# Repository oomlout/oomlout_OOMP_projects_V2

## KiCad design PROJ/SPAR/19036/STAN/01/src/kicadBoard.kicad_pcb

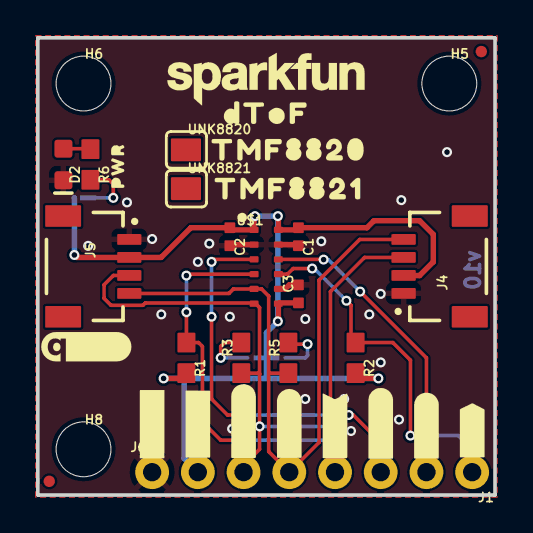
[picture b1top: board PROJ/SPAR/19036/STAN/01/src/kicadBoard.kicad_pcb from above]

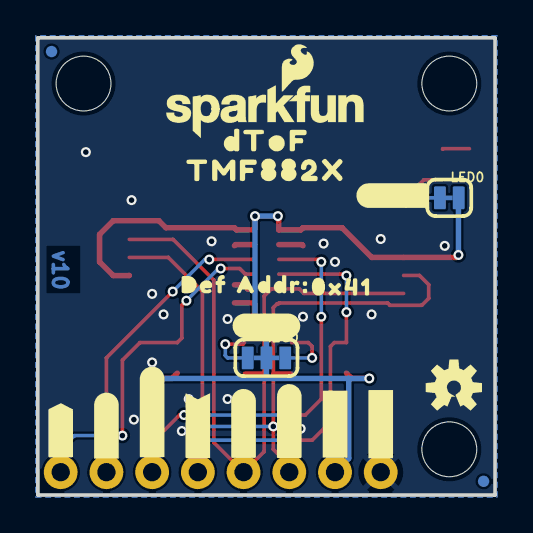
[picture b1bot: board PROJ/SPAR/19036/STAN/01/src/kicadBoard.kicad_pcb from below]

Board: 2 copper layers, 25.4 x 25.4 mm, 57 parts (21 on the bottom side), 12 nets.

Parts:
C1, C2, C3: 0.1uF; 0402-TIGHT
D2: RED; LED-0603
FD5, FD6, FD7, FD8: FIDUCIALUFIDUCIAL; FIDUCIAL-MICRO
FRAME2: FRAME-LETTER; CREATIVE_COMMONS
H5, H6, H8: STAND-OFFTIGHT; STAND-OFF-TIGHT
I2C0: I2C_PU; SMT-JUMPER_3_2-NC_TRACE_SILK
J1, J6: 1X04_NO_SILK
J4, J5: QWIIC_RIGHT_ANGLE; JST04_1MM_RA
LED0: LED; SMT-JUMPER_2_NC_TRACE_SILK
LOGO3: SFE_LOGO_NAME_FLAME.1_INCH; SFE_LOGO_NAME_FLAME_.1
LOGO4: OSHW-LOGOS; OSHW-LOGO-S
R1, R2: 10k; 0603
R3, R5: 2.2k; 0603
R6: 1k; 0603
U$1: TMF882X_TMF8820; TMF882X
U$2, U$16: #3V3#0
U$3, U$18: #GND#4
U$4, U$23: #SDA#6
U$5, U$21: #SCL#5
U$6: QWIIC_LOGO_5MM; QWIIC_5MM
U$7, U$17: #EN#7
U$8: #GP0#19
U$9, U$19: #GP1#8
U$10: ##INT##9
U$11, U$26: DTOF882188211
U$12: TMF88209
U$13: SFE_LOGO_NAME_.1
U$14: PWR882188212
U$15: #SYNC#8
U$20: #I2C#11
U$22: #LED#10
U$24: ##INT##8
U$25: TMF882188210
U$27: TMF882X882188211
U$28: DEF11
U$29: ADDR#12
U$30: 0X4113
UNK8820: PROD_ID_PASTE_SILK; PRODUCT_IDENT_PASTE_SILK
UNK8821: PROD_ID_NO-PASTE_SILK; PRODUCT_IDENT_NO_SILK

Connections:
3.3V: C1.1, C2.1, C3.1, I2C0.2, J4.2, J5.2, J6.2, LED0.2, R1.2, R2.2, U$1.P1, U$1.P7, U$1.P12
EN: J1.1, R2.1, U$1.P9
GND: C1.2, C2.2, C3.2, D2.C, J4.1, J5.1, J6.1, U$1.P2, U$1.P8, U$1.P11
GPIO0/SYNC: J1.3, U$1.P3
GPIO1: J1.2, U$1.P10
unnamed: D2.A, R6.1
unnamed: LED0.1, R6.2
unnamed: I2C0.3, R3.2
unnamed: I2C0.1, R5.2
SCL: J4.4, J5.4, J6.4, R5.1, U$1.P5
SDA: J4.3, J5.3, J6.3, R3.1, U$1.P6
~INT: J1.4, R1.1, U$1.P4

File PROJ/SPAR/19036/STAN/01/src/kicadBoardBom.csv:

"Id";"Designator";"Package";"Quantity";"Designation";"Supplier and ref";
1;"R6";"0603";1;"1k";;;
2;"U$10";"##INT##9";1;"";;;
3;"U$8";"#GP0#19";1;"";;;
4;"J5,J4";"JST04_1MM_RA";2;"QWIIC_RIGHT_ANGLE";;;
5;"FD8,FD7,FD5,FD6";"FIDUCIAL-MICRO";4;"FIDUCIALUFIDUCIAL";;;
6;"U$12";"TMF88209";1;"";;;
7;"J1,J6";"1X04_NO_SILK";2;"";;;
8;"H8,H6,H5";"STAND-OFF-TIGHT";3;"STAND-OFFTIGHT";;;
9;"U$9,U$19";"#GP1#8";2;"";;;
10;"R3,R5";"0603";2;"2.2k";;;
11;"UNK8820";"PRODUCT_IDENT_PASTE_SILK";1;"PROD_ID_PASTE_SILK";;;
12;"U$13";"SFE_LOGO_NAME_.1";1;"";;;
13;"R1,R2";"0603";2;"10k";;;
14;"C1,C2,C3";"0402-TIGHT";3;"0.1uF";;;
15;"U$11,U$26";"DTOF882188211";2;"";;;
16;"D2";"LED-0603";1;"RED";;;
17;"U$4,U$23";"#SDA#6";2;"";;;
18;"UNK8821";"PRODUCT_IDENT_NO_SILK";1;"PROD_ID_NO-PASTE_SILK";;;
19;"U$17,U$7";"#EN#7";2;"";;;
20;"U$25";"TMF882188210";1;"";;;
21;"FRAME2";"CREATIVE_COMMONS";1;"FRAME-LETTER";;;
22;"U$5,U$21";"#SCL#5";2;"";;;
23;"U$1";"TMF882X";1;"TMF882X_TMF8820";;;
24;"U$14";"PWR882188212";1;"";;;
25;"U$6";"QWIIC_5MM";1;"QWIIC_LOGO_5MM";;;
26;"U$3,U$18";"#GND#4";2;"";;;
27;"U$2,U$16";"#3V3#0";2;"";;;
28;"U$22";"#LED#10";1;"";;;
29;"LED0";"SMT-JUMPER_2_NC_TRACE_SILK";1;"LED";;;
30;"U$29";"ADDR#12";1;"";;;
31;"U$28";"DEF11";1;"";;;
32;"U$24";"##INT##8";1;"";;;
33;"U$27";"TMF882X882188211";1;"";;;
34;"U$30";"0X4113";1;"";;;
35;"LOGO4";"OSHW-LOGO-S";1;"OSHW-LOGOS";;;
36;"U$20";"#I2C#11";1;"";;;
37;"U$15";"#SYNC#8";1;"";;;
38;"I2C0";"SMT-JUMPER_3_2-NC_TRACE_SILK";1;"I2C_PU";;;
39;"LOGO3";"SFE_LOGO_NAME_FLAME_.1";1;"SFE_LOGO_NAME_FLAME.1_INCH";;;

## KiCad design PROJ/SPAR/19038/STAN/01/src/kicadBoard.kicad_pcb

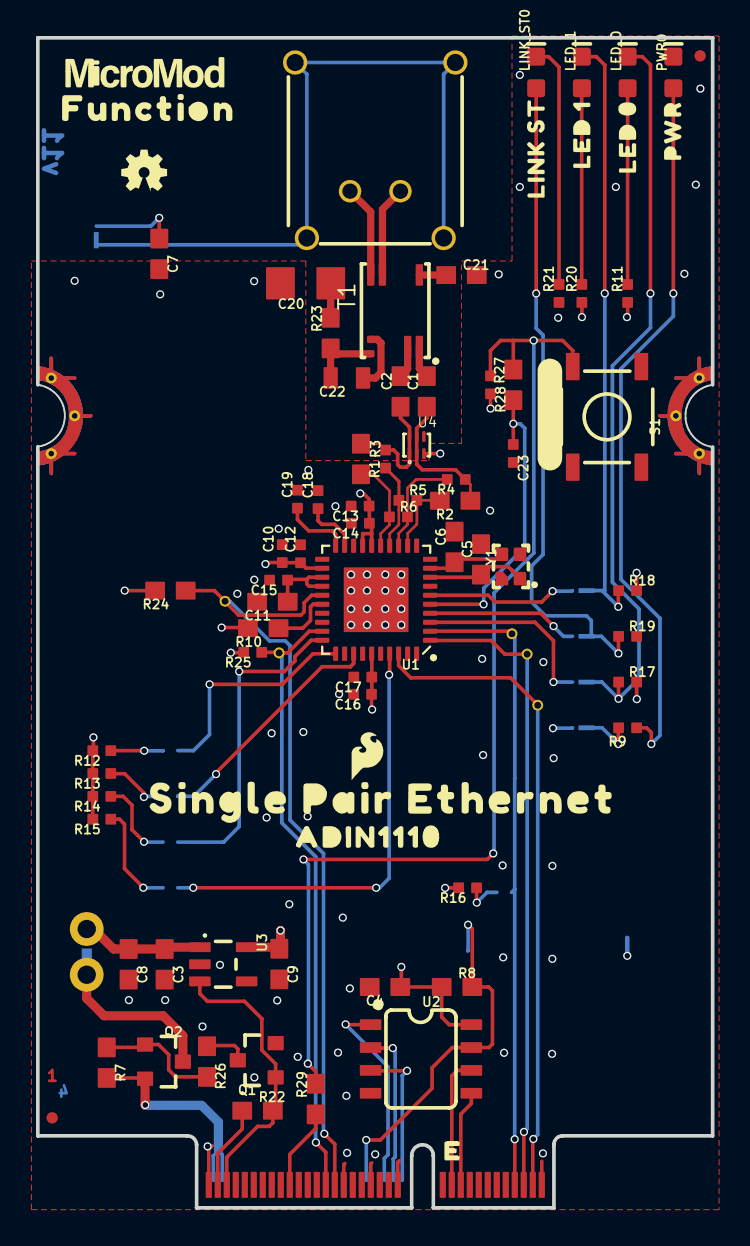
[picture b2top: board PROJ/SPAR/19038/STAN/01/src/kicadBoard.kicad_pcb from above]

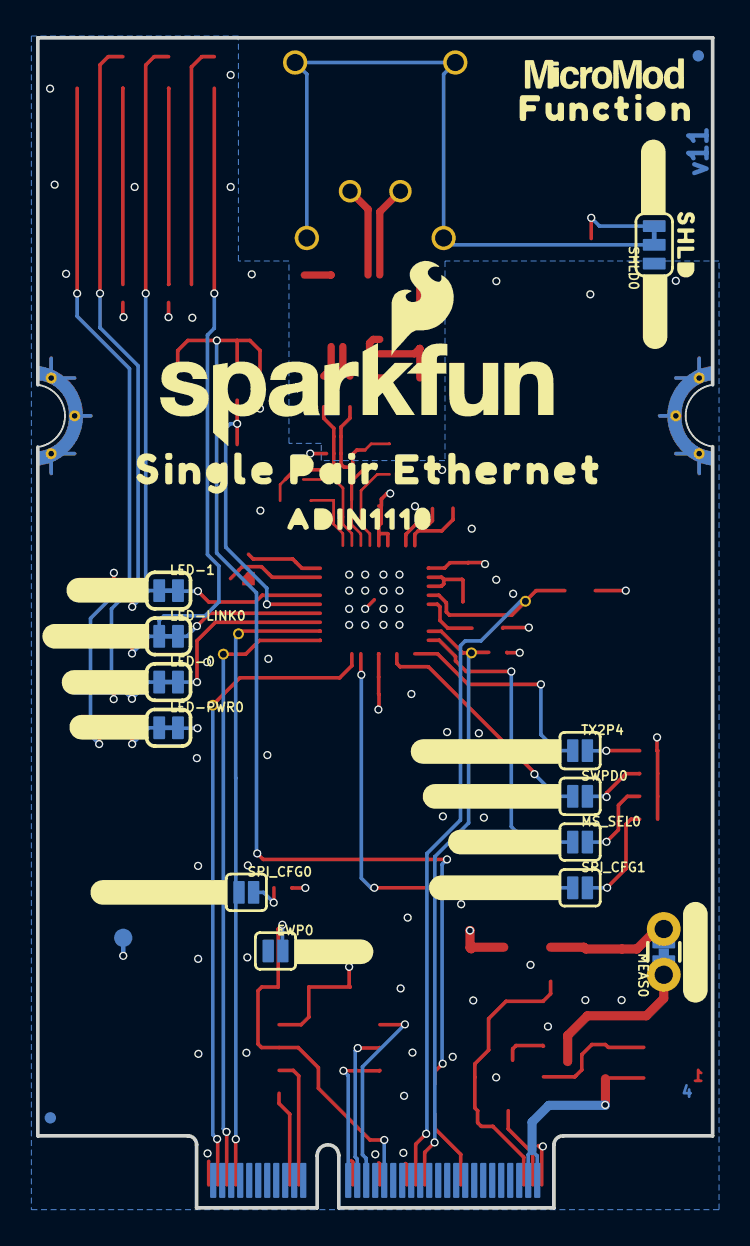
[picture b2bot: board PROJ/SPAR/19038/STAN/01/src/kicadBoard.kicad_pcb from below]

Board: 4 copper layers, 37.5 x 65.0 mm, 121 parts (34 on the bottom side), 65 nets.

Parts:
C1, C2: 0.22uF; 0603
C3, C4: 0.1uF; 0603
C5, C6: 10pF; 0603
C7: 3.3nF; 0603
C8, C9: 1.0uF; 0603
C10, C13, C15, C16, C18, C23: 0.1uF; 0402-TIGHT
C11: 0.68uF; 0603
C12, C14, C17: 10nF; 0402-TIGHT
C19: 1.0uF; 0402-TIGHT
C20: 1.0nF/2kV; 1206
C21: 0.1uF/50V; 0603
C22: 470nF/100V; 0805
CIPO0: TP_15TH
COPI0: TP_15TH
CS0: TP_15TH
EWP0: JUMPER-SMT_2_NO_SILK; SMT-JUMPER_2_NO_SILK
FD1, FD2, FD3, FD4: FIDUCIALUFIDUCIAL; FIDUCIAL-MICRO
FRAME1: FRAME-LEDGER; CREATIVE_COMMONS
INT0: TP_15TH
J1: IP20(RJ50); T1_INDUSTRIAL_JACK_AH_IP20
J2: MICROMOD_FUNCTION_STANDARD; M.2-CARD-E-22_FUNCTION_STANDARD
LED-0, LED-1: JUMPER-SMT_2_NC_TRACE_SILK; SMT-JUMPER_2_NC_TRACE_SILK
LED-LINK0: JUMPER-SMT_2_NC_TRACE_SILK; SMT-JUMPER_2_NC_TRACE_SILK
LED-PWR0: JUMPER-SMT_2_NC_TRACE_SILK; SMT-JUMPER_2_NC_TRACE_SILK
LED_0: Green; LED-0603
LED_1: Yellow; LED-0603
LINK_ST0: Blue; LED-0603
LOGO1: SFE_LOGO_NAME_FLAME.2_INCH; SFE_LOGO_NAME_FLAME_.2
LOGO2: SPECIAL_INSTRUCTIONS-ORDERING; ORDERING_INSTRUCTIONS
LOGO3: OSHW-LOGOMINI; OSHW-LOGO-MINI
MEAS0: JUMPER-COMBO_2_NC_TRACE; COMBO-JUMPER_2_NC_TRACE
MS_SEL0: SMT-JUMPER_2_NO_SILK
PWR0: Red; LED-0603
Q1: 220mA/50V/3.5Ω; SOT23-3
Q2: 20V/4.2A/52mΩ/1.4W; SOT23-3
R1, R2: 49.9; 0603
R3, R4: 5.1k; 0402-TIGHT
R5, R6: 10.2k; 0402-TIGHT
R7, R8, R22: 10k; 0603
R9, R11, R20, R21: 1k; 0402-TIGHT
R10, R24: 1.5k; 0603
R12, R13, R14, R15, R16, R17, R18, R19, R25: 4.7k; 0402-TIGHT
R23, R29: 100Ω; 0603
R26: 100; 0603
R27: 4.7k; 0603
R28: 100k; 0402-TIGHT
S1: RESET; TACTILE_SWITCH_SMD_5.2MM
SHLD0: SMT-JUMPER_3_1-NC_TRACE_SILK
SPI0: TP_15TH
SPI_CFG0, SPI_CFG1: SMT-JUMPER_2_NO_SILK
SWPD0: SMT-JUMPER_2_NO_SILK
T1: WE-STST; WE_STST_TRANSFORMER_1_1_SMD_3.2X4.7MM_74930030
TP1: TEST-POINT3X4; PAD.03X.04
TX2P4: SMT-JUMPER_2_NO_SILK
U1: ADIN1110; LFCSP-40
U2: EEPROM; SO08
U3: 3.3V; SOT23-5
U4: WE-TVS; WE_TVS_1.0X1.2MM
U$1: #RESET#0
U$4, U$21: ADIN11100
U$5: SFE_LOGO_FLAME_.1
U$6: #PWR#19
U$7: PWR0
U$8: SHLD11
U$9: #EWP#18
U$10: #LED0#20
U$11: #GND#16
U$12: #CAP#17
U$13: ##TX2P4_EN##4
U$14: #SPI_CFG1#0
U$15: #MS_SEL#2
U$16: #SPI_CFG0#0
U$17, U$18: SINGLE_PAIR_ETHERNET0
U$22: ##SWPD_EN##4
U$23: LED_03
U$24, U$26: FUNCTION0
U$25: LED_14
U$27: LINK_ST15
U$28: #MEAS#3
U$29: #LED1#21
U$31: #LINKST#2
U$37, U$63: MICROMOD_LOGO_.35
Y1: 25MHz; CRYSTAL-SMD-2.0X1.6MM-WE

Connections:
1.1V: C11.1, C15.1, U1.23, U1.24
3.3V: C4.1, C9.1, C10.1, C12.1, C13.1, C14.1, C16.1, C17.1, LED-PWR0.2, R8.1, R10.2, R11.1, R12.2, R13.2, R14.2, R15.2, R16.2, R17.2, R18.2, R20.1, R24.2, R25.2, R28.2, TP1.1, U1.16, U1.17, U1.22, U1.35, U2.8, U3.5
3.3V_IN: J2.73, R22.1
A0: J2.36, U2.1
A1: J2.34, U2.2
A2: J2.32, U2.3
DA+: J1.1, T1.7
DA-: J1.2, T1.6
EWP: EWP0.2, J2.40, R8.2, U2.7
GND: C3.2, C4.2, C5.2, C6.2, C7.2, C8.2, C9.2, C10.2, C11.2, C12.2, C13.2, C14.2, C15.2, C16.2, C17.2, C18.2, C19.2, C20.2, C21.2, C23.2, EWP0.1, J2.1, J2.33, J2.39, J2.45, J2.75, J2.GND1, J2.GND2, J2.GND3, J2.GND4, J2.GND5, J2.GND6, PWR0.C, Q1.2, R19.2, R21.1, S1.1, SHLD0.1, U1.EP, U2.4, U3.2, U4.3, Y1.2, Y1.4
I2C_SCL: J2.21, U2.6
I2C_SDA: J2.19, U2.5
LED_0: LED-0.2, U1.3
LED_1: LED-1.2, U1.6
LINK_ST: LED-LINK0.2, U1.4
MS_SEL: MS_SEL0.1, U1.30
unnamed: MEAS0.1, MEAS0.3, Q2.3
unnamed: C3.1, C8.1, MEAS0.2, MEAS0.4, U3.1
unnamed: C21.1, T1.5
unnamed: C22.1, T1.4
unnamed: LED-LINK0.1, LINK_ST0.A, R19.1
unnamed: LED-1.1, LED_1.C, R18.1
unnamed: C22.2, R23.1, T1.3
unnamed: C20.1, R23.2
unnamed: LED-0.1, LED_0.C, R17.1
unnamed: Q1.3, R26.1
unnamed: Q2.1, R7.1, R26.2
unnamed: C5.1, U1.8, Y1.1
unnamed: C23.1, R27.1, U1.5
unnamed: C6.1, U1.9, Y1.3
unnamed: R27.2, R28.1, R29.2, S1.3
unnamed: R10.1, U1.26
unnamed: LED-PWR0.1, R9.2
unnamed: PWR0.A, R9.1
unnamed: C18.1, U1.19
unnamed: C19.1, U1.20
unnamed: LED_0.A, R11.2
unnamed: C1.1, R2.1, R4.1, U4.2, U4.5
unnamed: MS_SEL0.2, R14.1
unnamed: R13.1, SWPD0.2
unnamed: R12.1, TX2P4.2
unnamed: R16.1, SPI_CFG0.2
unnamed: R15.1, SPI_CFG1.2
unnamed: LED_1.A, R20.2
unnamed: C2.1, R1.1, R3.2, U4.1, U4.6
unnamed: C1.2, T1.1
unnamed: LINK_ST0.C, R21.2
unnamed: C2.2, T1.2
unnamed: R4.2, R6.2, U1.13
unnamed: R3.1, R5.1, U1.14
unnamed: R1.2, R6.1, U1.15
unnamed: R2.2, R5.2, U1.12
unnamed: C7.1, SHLD0.3
unnamed: J1.S1, J1.S2, J1.S3, J1.S4, SHLD0.2
PWR_EN: J2.71, Q1.1, R22.2, U3.3
SPI_CFG1: SPI_CFG1.1, U1.37
SPI_PICO: COPI0.1, J2.5, U1.1
SPI_POCI/SPI_CFG0: CIPO0.1, J2.7, SPI_CFG0.1, U1.2
SPI_SCK: J2.3, SPI0.1, U1.38
VCC_IN: J2.72, J2.74, Q2.2, R7.2
~CS: CS0.1, J2.49, R25.1, U1.29
~INT: INT0.1, J2.47, R24.1, U1.25
~RESET: J2.57, R29.1
~SWPD_EN: SWPD0.1, U1.33
~TX2P4_EN: TX2P4.1, U1.31

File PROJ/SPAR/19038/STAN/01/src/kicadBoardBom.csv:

"Id";"Designator";"Package";"Quantity";"Designation";"Supplier and ref";
1;"U$27";"LINK_ST15";1;"";;;
2;"R18,R25,R12,R17,R19,R16,R13,R14,R15";"0402-TIGHT";9;"4.7k";;;
3;"FRAME1";"CREATIVE_COMMONS";1;"FRAME-LEDGER";;;
4;"U$7";"PWR0";1;"";;;
5;"C2,C1";"0603";2;"0.22uF";;;
6;"Q2";"SOT23-3";1;"20V/4.2A/52mΩ/1.4W";;;
7;"C8,C9";"0603";2;"1.0uF";;;
8;"U1";"LFCSP-40";1;"ADIN1110";;;
9;"C10,C13,C16,C23,C15,C18";"0402-TIGHT";6;"0.1uF";;;
10;"R20,R11,R9,R21";"0402-TIGHT";4;"1k";;;
11;"R23,R29";"0603";2;"100Ω";;;
12;"CIPO0,INT0,SPI0,COPI0,CS0";"TP_15TH";5;"";;;
13;"R26";"0603";1;"100";;;
14;"S1";"TACTILE_SWITCH_SMD_5.2MM";1;"RESET";;;
15;"R5,R6";"0402-TIGHT";2;"10.2k";;;
16;"U3";"SOT23-5";1;"3.3V";;;
17;"C17,C12,C14";"0402-TIGHT";3;"10nF";;;
18;"LOGO3";"OSHW-LOGO-MINI";1;"OSHW-LOGOMINI";;;
19;"R1,R2";"0603";2;"49.9";;;
20;"LED_1";"LED-0603";1;"Yellow";;;
21;"U$25";"LED_14";1;"";;;
22;"C19";"0402-TIGHT";1;"1.0uF";;;
23;"LED_0";"LED-0603";1;"Green";;;
24;"R7,R22,R8";"0603";3;"10k";;;
25;"U$17,U$18";"SINGLE_PAIR_ETHERNET0";2;"";;;
26;"C5,C6";"0603";2;"10pF";;;
27;"PWR0";"LED-0603";1;"Red";;;
28;"R24,R10";"0603";2;"1.5k";;;
29;"U$5";"SFE_LOGO_FLAME_.1";1;"";;;
30;"FD2,FD1,FD4,FD3";"FIDUCIAL-MICRO";4;"FIDUCIALUFIDUCIAL";;;
31;"T1";"WE_STST_TRANSFORMER_1_1_SMD_3.2X4.7MM_74930030";1;"WE-STST";;;
32;"LOGO2";"ORDERING_INSTRUCTIONS";1;"SPECIAL_INSTRUCTIONS-ORDERING";;;
33;"U$63,U$37";"MICROMOD_LOGO_.35";2;"";;;
34;"U$26,U$24";"FUNCTION0";2;"";;;
35;"R3,R4";"0402-TIGHT";2;"5.1k";;;
36;"U4";"WE_TVS_1.0X1.2MM";1;"WE-TVS";;;
37;"C11";"0603";1;"0.68uF";;;
38;"R27";"0603";1;"4.7k";;;
39;"U$23";"LED_03";1;"";;;
40;"U$1";"#RESET#0";1;"";;;
41;"C3,C4";"0603";2;"0.1uF";;;
42;"Q1";"SOT23-3";1;"220mA/50V/3.5Ω";;;
43;"C20";"1206";1;"1.0nF/2kV";;;
44;"R28";"0402-TIGHT";1;"100k";;;
45;"C7";"0603";1;"3.3nF";;;
46;"U2";"SO08";1;"EEPROM";;;
47;"C22";"0805";1;"470nF/100V";;;
48;"C21";"0603";1;"0.1uF/50V";;;
49;"LINK_ST0";"LED-0603";1;"Blue";;;
50;"Y1";"CRYSTAL-SMD-2.0X1.6MM-WE";1;"25MHz";;;
51;"U$4,U$21";"ADIN11100";2;"";;;
52;"J2";"M.2-CARD-E-22_FUNCTION_STANDARD";1;"MICROMOD_FUNCTION_STANDARD";;;
53;"J1";"T1_INDUSTRIAL_JACK_AH_IP20";1;"IP20(RJ50)";;;
54;"LOGO1";"SFE_LOGO_NAME_FLAME_.2";1;"SFE_LOGO_NAME_FLAME.2_INCH";;;
55;"LED-1,LED-0,LED-LINK0,LED-PWR0";"SMT-JUMPER_2_NC_TRACE_SILK";4;"JUMPER-SMT_2_NC_TRACE_SILK";;;
56;"SPI_CFG0,SPI_CFG1,TX2P4,SWPD0,MS_SEL0";"SMT-JUMPER_2_NO_SILK";5;"";;;
57;"U$8";"SHLD11";1;"";;;
58;"U$15";"#MS_SEL#2";1;"";;;
59;"U$9";"#EWP#18";1;"";;;
60;"U$12";"#CAP#17";1;"";;;
61;"MEAS0";"COMBO-JUMPER_2_NC_TRACE";1;"JUMPER-COMBO_2_NC_TRACE";;;
62;"U$6";"#PWR#19";1;"";;;
63;"TP1";"PAD.03X.04";1;"TEST-POINT3X4";;;
64;"U$29";"#LED1#21";1;"";;;
65;"U$10";"#LED0#20";1;"";;;
66;"U$14";"#SPI_CFG1#0";1;"";;;
67;"U$22";"##SWPD_EN##4";1;"";;;
68;"EWP0";"SMT-JUMPER_2_NO_SILK";1;"JUMPER-SMT_2_NO_SILK";;;
69;"U$13";"##TX2P4_EN##4";1;"";;;
70;"U$28";"#MEAS#3";1;"";;;
71;"SHLD0";"SMT-JUMPER_3_1-NC_TRACE_SILK";1;"";;;
72;"U$11";"#GND#16";1;"";;;
73;"U$31";"#LINKST#2";1;"";;;
74;"U$16";"#SPI_CFG0#0";1;"";;;

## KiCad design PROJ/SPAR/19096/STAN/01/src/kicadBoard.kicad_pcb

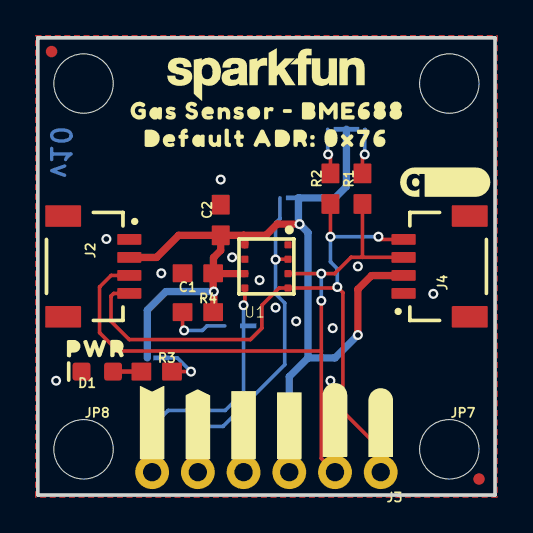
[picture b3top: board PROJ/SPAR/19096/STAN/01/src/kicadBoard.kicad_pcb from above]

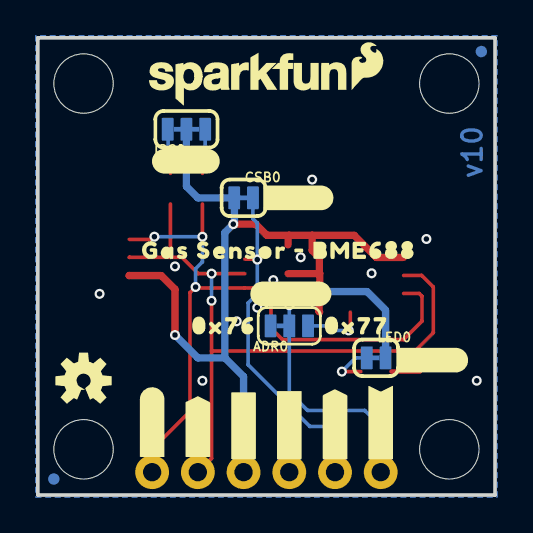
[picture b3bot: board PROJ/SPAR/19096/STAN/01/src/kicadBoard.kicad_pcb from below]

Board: 2 copper layers, 25.4 x 25.4 mm, 52 parts (22 on the bottom side), 11 nets.

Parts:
ADR0: JUMPER-SMT_3_1-NC_TRACE_SILK; SMT-JUMPER_3_1-NC_TRACE_SILK
C1, C2: 0.1uF; 0603
CSB0: JUMPER-SMT_2_NC_TRACE_SILK; SMT-JUMPER_2_NC_TRACE_SILK
D1: RED; LED-0603
FRAME1: FRAME-LETTER; CREATIVE_COMMONS
I2C0: JUMPER-SMT_3_2-NC_TRACE_SILK; SMT-JUMPER_3_2-NC_TRACE_SILK
J2, J4: QWIIC_RA; JST04_1MM_RA
J3: 1X06_NO_SILK
JP1, JP2, JP5, JP6: FIDUCIALUFIDUCIAL; FIDUCIAL-MICRO
JP3, JP4, JP7, JP8: STAND-OFF
LED0: JUMPER-SMT_2_NC_TRACE_SILK; SMT-JUMPER_2_NC_TRACE_SILK
LOGO1: SPECIAL_INSTRUCTIONS-ORDERING; ORDERING_INSTRUCTIONS
LOGO2: QWIIC_LOGO_5MM; QWIIC_5MM
LOGO3, LOGO6: SFE_LOGO_NAME.1_INCH; SFE_LOGO_NAME_.1
LOGO4: SFE_LOGO_FLAME.1_INCH; SFE_LOGO_FLAME_.1
LOGO5: OSHW-LOGOS; OSHW-LOGO-S
R1, R2: 2.2k; 0603
R3: 1k; 0603
R4: 10k; 0603
U1: BME688LGA; LGA_8PIN
U$1, U$33: #GND#0
U$2, U$16: #SDO#0
U$3: #CSB#0
U$5: PWR0
U$6: #I2C#0
U$7, U$10: GAS_SENSOR_#_BME6880
U$8: #LED#0
U$9: 0X760
U$11: #ADR#0
U$12: DEFAULT_ADR#_0X760
U$13: 0X770
U$14, U$15: #3V3#0
U$19: #SDI#0
U$20: #SCK#0
U$21, U$22: ##CSB##0
U$35: #SDA#0
U$36: #SCL#0

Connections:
3.3V: C1.1, C2.1, CSB0.1, I2C0.2, J2.2, J3.3, J4.2, LED0.2, R4.2, U1.6, U1.8
GND: ADR0.3, C1.2, C2.2, D1.C, J2.1, J3.4, J4.1, U1.1, U1.7
unnamed: LED0.1, R3.2
unnamed: I2C0.3, R1.2
unnamed: D1.A, R3.1
unnamed: I2C0.1, R2.2
unnamed: ADR0.1, R4.1
SCL/SCK: J2.4, J3.1, J4.4, R2.1, U1.4
SDI/SDA: J2.3, J3.2, J4.3, R1.1, U1.3
SDO: ADR0.2, J3.6, U1.5
~CSB: CSB0.2, J3.5, U1.2

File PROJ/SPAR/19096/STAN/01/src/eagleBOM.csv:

"Part";"Value";"Device";"Package";"Description";"DESIGNER";"PROD_ID";"REV";"VALUE";
"ADR";"JUMPER-SMT_3_1-NC_TRACE_SILK";"JUMPER-SMT_3_1-NC_TRACE_SILK";"SMT-JUMPER_3_1-NC_TRACE_SILK";"Normally closed trace jumper (1 of 2 connections)";"";"";"";"";
"C1";"0.1uF";"0.1UF-0603-100V-10%";"0603";"0.1µF ceramic capacitors";"";"CAP-08390";"";"0.1uF";
"C2";"0.1uF";"0.1UF-0603-100V-10%";"0603";"0.1µF ceramic capacitors";"";"CAP-08390";"";"0.1uF";
"CSB";"JUMPER-SMT_2_NC_TRACE_SILK";"JUMPER-SMT_2_NC_TRACE_SILK";"SMT-JUMPER_2_NC_TRACE_SILK";"Normally closed trace jumper";"";"";"";"";
"D1";"RED";"LED-RED0603";"LED-0603";"Red SMD LED";"";"DIO-00819";"";"RED";
"FRAME1";"FRAME-LETTER";"FRAME-LETTER";"CREATIVE_COMMONS";"Schematic Frame - Letter";"";"";"";"";
"I2C";"JUMPER-SMT_3_2-NC_TRACE_SILK";"JUMPER-SMT_3_2-NC_TRACE_SILK";"SMT-JUMPER_3_2-NC_TRACE_SILK";"Normally closed trace jumper (2 of 2 connections)";"";"";"";"";
"J2";"QWIIC_RA";"QWIIC_CONNECTORJS-1MM";"JST04_1MM_RA";"SparkFun I2C Standard Qwiic Connector";"";"CONN-13694";"";"QWIIC_RIGHT_ANGLE";
"J3";"";"CONN_06NO_SILK_NO_POP";"1X06_NO_SILK";"Multi connection point. Often used as Generic Header-pin footprint for 0.1 inch spaced/style header connections";"";"";"";"";
"J4";"QWIIC_RA";"QWIIC_CONNECTORJS-1MM";"JST04_1MM_RA";"SparkFun I2C Standard Qwiic Connector";"";"CONN-13694";"";"QWIIC_RIGHT_ANGLE";
"JP1";"FIDUCIALUFIDUCIAL";"FIDUCIALUFIDUCIAL";"FIDUCIAL-MICRO";"Fiducial Alignment Points";"";"";"";"";
"JP2";"FIDUCIALUFIDUCIAL";"FIDUCIALUFIDUCIAL";"FIDUCIAL-MICRO";"Fiducial Alignment Points";"";"";"";"";
"JP3";"STAND-OFF";"STAND-OFF";"STAND-OFF";"Stand Off";"";"";"";"";
"JP4";"STAND-OFF";"STAND-OFF";"STAND-OFF";"Stand Off";"";"";"";"";
"JP5";"FIDUCIALUFIDUCIAL";"FIDUCIALUFIDUCIAL";"FIDUCIAL-MICRO";"Fiducial Alignment Points";"";"";"";"";
"JP6";"FIDUCIALUFIDUCIAL";"FIDUCIALUFIDUCIAL";"FIDUCIAL-MICRO";"Fiducial Alignment Points";"";"";"";"";
"JP7";"STAND-OFF";"STAND-OFF";"STAND-OFF";"Stand Off";"";"";"";"";
"JP8";"STAND-OFF";"STAND-OFF";"STAND-OFF";"Stand Off";"";"";"";"";
"LED";"JUMPER-SMT_2_NC_TRACE_SILK";"JUMPER-SMT_2_NC_TRACE_SILK";"SMT-JUMPER_2_NC_TRACE_SILK";"Normally closed trace jumper";"";"";"";"";
"LOGO1";"SPECIAL_INSTRUCTIONS-ORDERING";"SPECIAL_INSTRUCTIONS-ORDERING";"ORDERING_INSTRUCTIONS";"Special Ordering/Production Instructions Alert";"";"";"";"";
"LOGO2";"QWIIC_LOGO_5MM";"QWIIC_LOGO_5MM";"QWIIC_5MM";"Qwiic Logos for placement on schematic and PCB. The 5.5mm silk logo is best for placing next to Qwiic connector.";"";"";"";"";
"LOGO3";"SFE_LOGO_NAME.1_INCH";"SFE_LOGO_NAME.1_INCH";"SFE_LOGO_NAME_.1";"SparkFun Font Logo";"";"";"";"";
"LOGO4";"SFE_LOGO_FLAME.1_INCH";"SFE_LOGO_FLAME.1_INCH";"SFE_LOGO_FLAME_.1";"SparkFun Flame Logo";"";"";"";"";
"LOGO5";"OSHW-LOGOS";"OSHW-LOGOS";"OSHW-LOGO-S";"Open-Source Hardware (OSHW) Logo";"";"";"";"";
"LOGO6";"SFE_LOGO_NAME.1_INCH";"SFE_LOGO_NAME.1_INCH";"SFE_LOGO_NAME_.1";"SparkFun Font Logo";"";"";"";"";
"R1";"2.2k";"2.2KOHM-0603-1/10W-1%";"0603";"2.2kΩ resistor";"";"RES-08272";"";"2.2k";
"R2";"2.2k";"2.2KOHM-0603-1/10W-1%";"0603";"2.2kΩ resistor";"";"RES-08272";"";"2.2k";
"R3";"1k";"1KOHM-0603-1/10W-1%";"0603";"1kΩ resistor";"";"RES-07856";"";"1k";
"R4";"10k";"10KOHM-0603-1/10W-1%";"0603";"10kΩ resistor";"";"RES-00824";"";"10k";
"U1";"BME688LGA";"BME688LGA";"LGA_8PIN";"BME688 gas sensor from Bosch.";"";"";"";"";

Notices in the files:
parts and their libraries:
HTTPS://CREATIVECOMMONS.ORG/LICENSES/BY-SA/4.0
RELEASED UNDER THE CREATIVE COMMONS ATTRIBUTION SHARE-ALIKE 4.0 LICENSE
